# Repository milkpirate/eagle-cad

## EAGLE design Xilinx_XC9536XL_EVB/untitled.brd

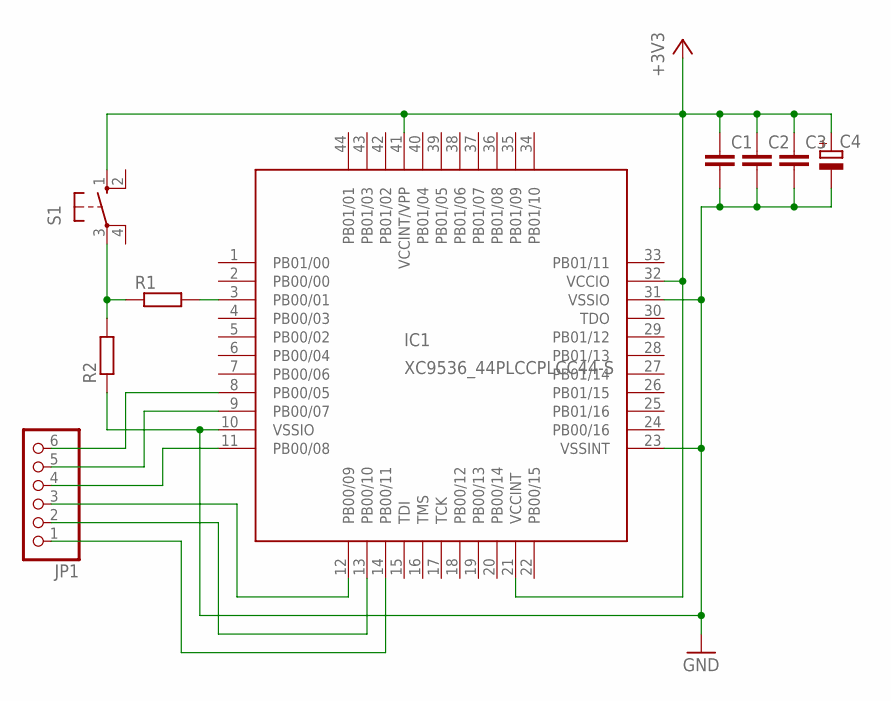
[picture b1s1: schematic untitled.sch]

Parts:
C1, C2, C3: C-EU050-025X075; C050-025X075
C4: CPOL-EUE2.5-6; E2,5-6
IC1: XC9536_44PLCCPLCC44-S; PLCC-S44
JP1: PINHD-1X6; 1X06
R1, R2: R-EU_0204/7; 0204/7
S1: 10-XX; B3F-10XX

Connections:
+3V3: C1.1, C2.1, C3.1, C4.+, IC1.21 (VCCINT), IC1.32 (VCCIO), IC1.41 (VCCINT/VPP), S1.1 (S)
GND: C1.2, C2.2, C3.2, C4.-, IC1.10 (VSSIO), IC1.23 (VSSINT), IC1.31 (VSSIO), R2.1
unnamed: IC1.8 (PB00/05), JP1.6
unnamed: IC1.9 (PB00/07), JP1.5
unnamed: IC1.3 (PB00/01), R1.2
unnamed: R1.1, R2.2, S1.3
unnamed: IC1.11 (PB00/08), JP1.4
unnamed: IC1.12 (PB00/09), JP1.3
unnamed: IC1.13 (PB00/10), JP1.2
unnamed: IC1.14 (PB00/11), JP1.1

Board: 2 copper layers, 9 parts (0 on the bottom side), 10 nets, no tracks yet.

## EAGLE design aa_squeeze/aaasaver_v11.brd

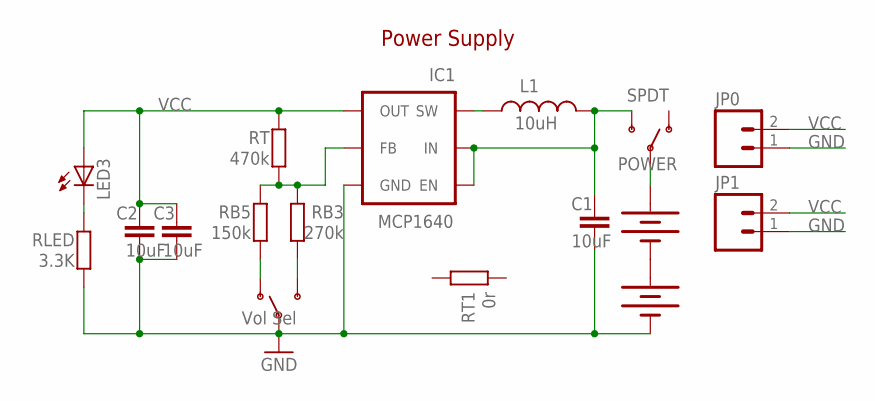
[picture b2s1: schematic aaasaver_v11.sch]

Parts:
AA1, AA2: BATTERYAAA; BATTERY-AAA
C1, C2, C3: 10uF; C0805
IC1: MCP1640; TSOT23-6
JP0, JP1: M021X02_NO_SILK; 1X02_NO_SILK
L1: 10uH; INDUCTOR_D45
LED3: 0805; CHIPLED_1206
POWER: SPDT; SWITCH-SPDT-SMD
RB3: 270k; R0805
RB5: 150k; R0805
RLED: 3.3K; R0805
RT: 470k; R0805
RT1: 0r; R1206
VOL1: Vol Sel; SWITCH-SPDT-SMD

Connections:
GND: AA2.GND@1 (-), C1.2, C2.2, C3.2, IC1.2 (GND), JP0.1, JP1.1, RLED.1, VOL1.2
unnamed: IC1.4 (FB), RB3.2, RB5.2, RT.1
unnamed: RB5.1, VOL1.1 (O)
unnamed: RB3.1, VOL1.3 (S)
unnamed: AA1.PWR@1 (+), POWER.2
unnamed: LED3.C, RLED.2
unnamed: AA1.GND@1 (-), AA2.PWR@1 (+)
unnamed: IC1.1 (SW), L1.P$2 (2)
PWR: C1.1, IC1.3 (EN), IC1.6 (IN), L1.P$1 (1), POWER.3 (S)
VCC: C2.1, C3.1, IC1.5 (OUT), JP0.2, JP1.2, LED3.A, RT.2

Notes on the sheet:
Power Supply

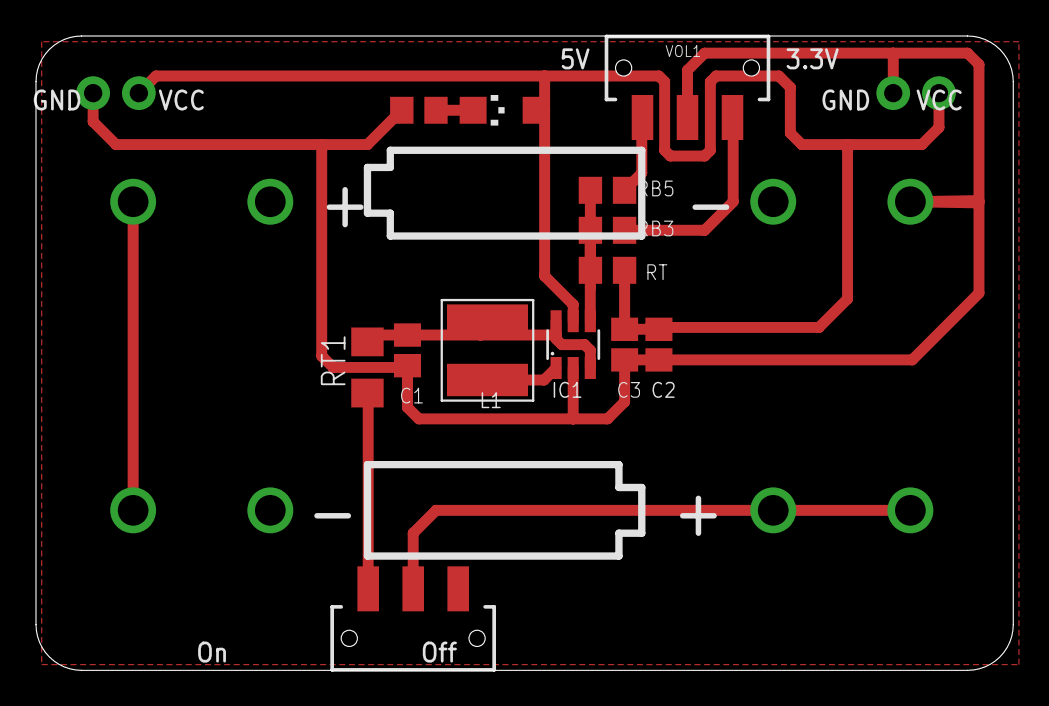
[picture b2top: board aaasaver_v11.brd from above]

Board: 2 copper layers, 54.3 x 35.2 mm, 17 parts (0 on the bottom side), 10 nets.

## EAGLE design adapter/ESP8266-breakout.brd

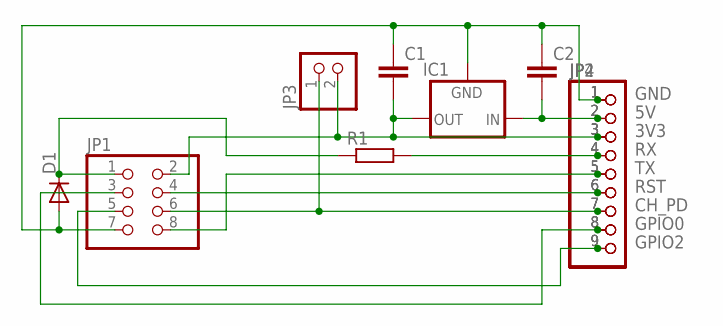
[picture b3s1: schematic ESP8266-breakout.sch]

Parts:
C1, C2: C-EU025-025X050; C025-025X050
D1: DIODE-D-5; D-5
IC1: V_REG_78XX-TO-220; TO-220-ALT
JP1: PINHD-2X4; 2X04
JP2, JP4: PINHD-1X9; 1X09
JP3: PINHD-1X2; 1X02
R1: R-EU_0204/7; 0204/7

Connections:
3V3: C1.2, IC1.OUT, JP1.2, JP2.3, JP3.2, JP4.3
5V: C2.2, IC1.IN, JP2.2, JP4.2
CH_PD: JP1.6, JP2.7, JP3.1, JP4.7
GND: C1.1, C2.1, D1.A, IC1.GND, JP1.7, JP2.1, JP4.1
GPIO0: JP1.3, JP2.8, JP4.8
GPIO2: JP1.5, JP2.9, JP4.9
unnamed: D1.C, JP1.1, R1.1
RST: JP1.4, JP2.6, JP4.6
RX: JP2.4, JP4.4, R1.2
TX: JP1.8, JP2.5, JP4.5

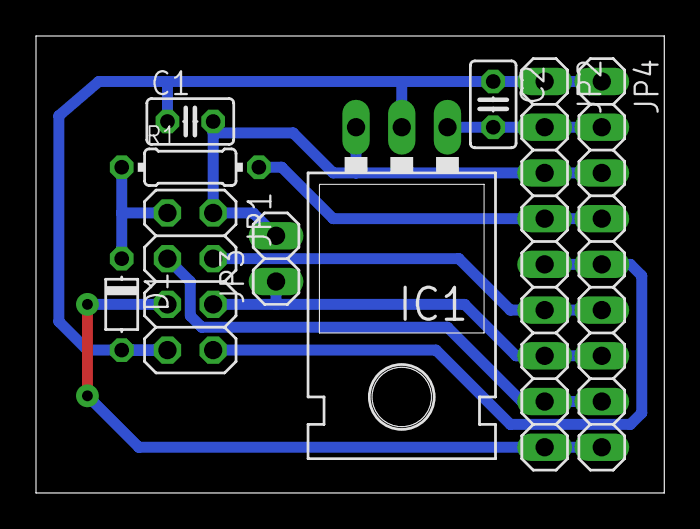
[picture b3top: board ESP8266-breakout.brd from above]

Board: 2 copper layers, 34.9 x 25.4 mm, 9 parts (0 on the bottom side), 10 nets.

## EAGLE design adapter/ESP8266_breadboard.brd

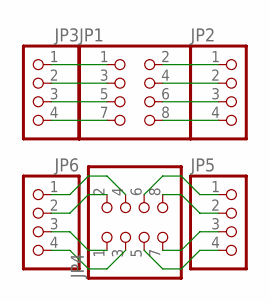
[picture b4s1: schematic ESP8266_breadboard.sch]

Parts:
JP1, JP4: PINHD-2X4; 2X04
JP2, JP3, JP5, JP6: PINHD-1X4; 1X04

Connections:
unnamed: JP1.2, JP2.1
unnamed: JP1.4, JP2.2
unnamed: JP1.6, JP2.3
unnamed: JP1.8, JP2.4
unnamed: JP1.1, JP3.1
unnamed: JP1.3, JP3.2
unnamed: JP1.5, JP3.3
unnamed: JP1.7, JP3.4
unnamed: JP4.2, JP6.2
unnamed: JP4.4, JP6.1
unnamed: JP4.1, JP6.3
unnamed: JP4.3, JP6.4
unnamed: JP4.8, JP5.2
unnamed: JP4.7, JP5.3
unnamed: JP4.6, JP5.1
unnamed: JP4.5, JP5.4

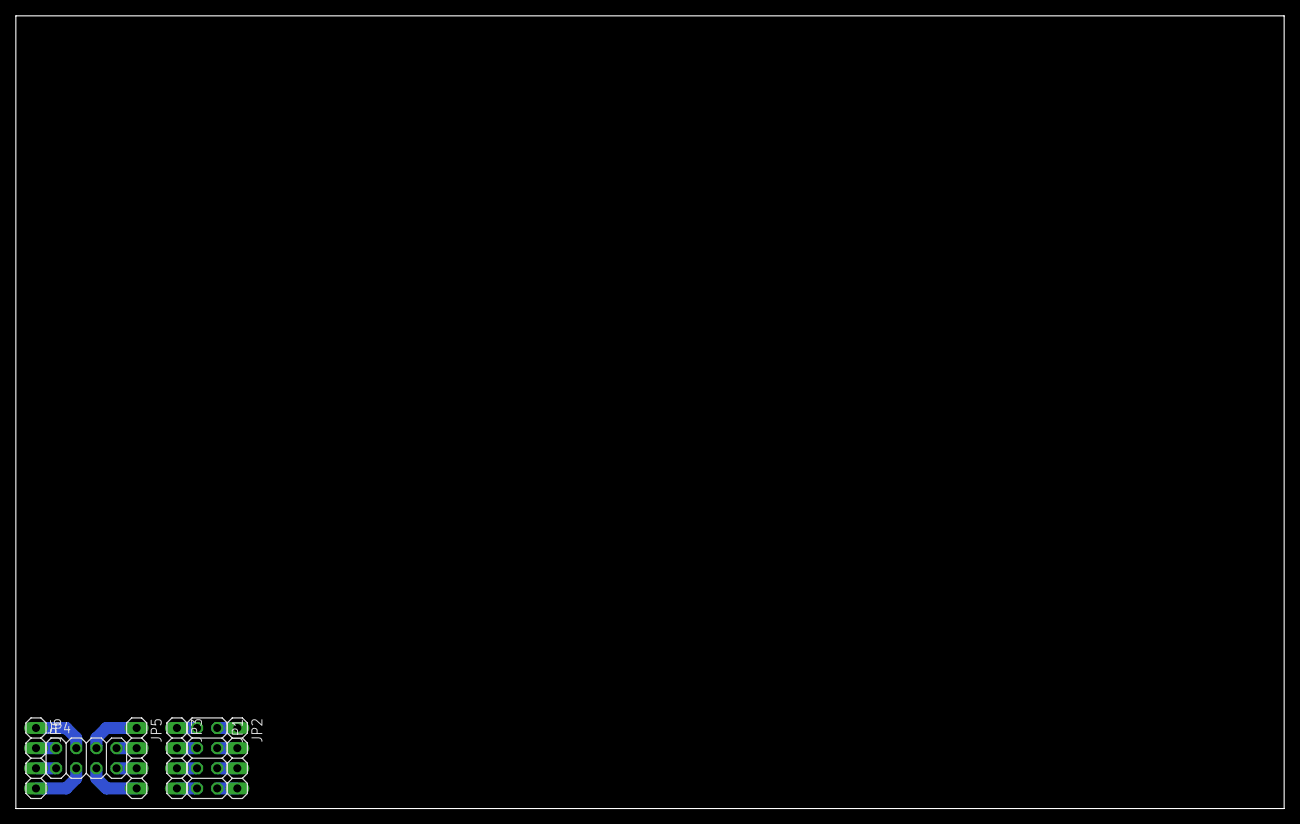
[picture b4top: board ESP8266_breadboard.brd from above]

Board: 2 copper layers, 160.0 x 100.0 mm, 6 parts (0 on the bottom side), 16 nets.

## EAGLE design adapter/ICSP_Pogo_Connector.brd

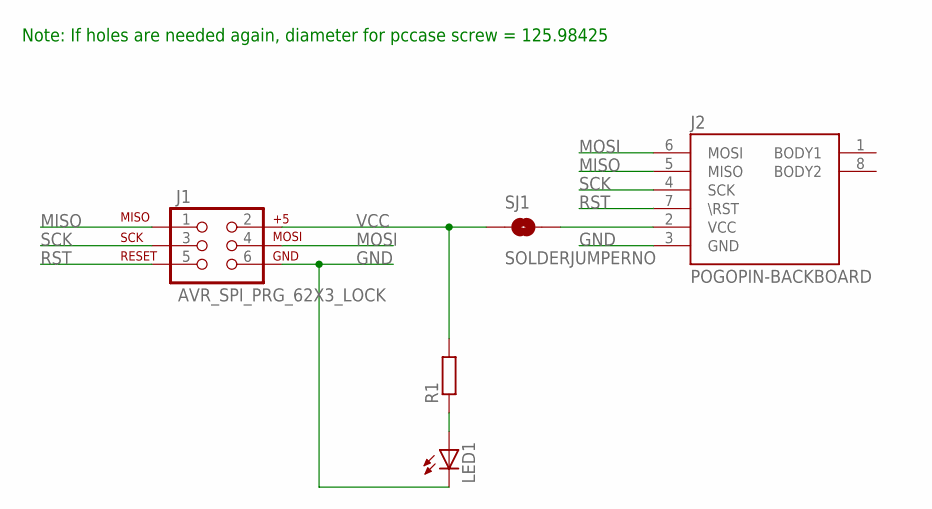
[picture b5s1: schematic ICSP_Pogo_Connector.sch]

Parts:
J1: AVR_SPI_PRG_62X3_LOCK; 2X3_LOCK
J2: POGOPIN-BACKBOARD; POGOPROG-BACKMOUNT
LED1: LEDCHIP-LED0805; CHIP-LED0805
R1: R-EU_M0805; M0805
SJ1: SOLDERJUMPERNO; SJ_2S-NO

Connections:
GND: J1.6, J2.3 (GND), LED1.C
MISO: J1.1, J2.5 (MISO)
MOSI: J1.4, J2.6 (MOSI)
unnamed: J2.2 (VCC), SJ1.2
unnamed: LED1.A, R1.1
RST: J1.5, J2.7 (\RST)
SCK: J1.3, J2.4 (SCK)
VCC: J1.2, R1.2, SJ1.1

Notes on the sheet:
Note: If holes are needed again, diameter for pccase screw = 125.98425

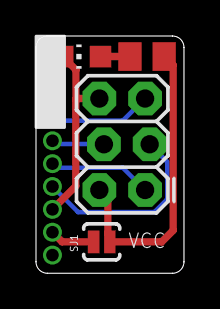
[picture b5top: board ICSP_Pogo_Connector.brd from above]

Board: 2 copper layers, 8.2 x 13.2 mm, 6 parts (1 on the bottom side), 8 nets.

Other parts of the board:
U$2: POGOPROG_LOGO

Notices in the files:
parts and their libraries:
SparkFun-PowerIC: Licensing: CC v3.0 Share-Alike You are welcome to use this library for commercial purposes.
